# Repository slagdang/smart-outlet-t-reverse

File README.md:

# Smart switched outlet (2025) teardown

## History and product overview

A smart switched outlet is actually a device that plugs into a non-switched
outlet and has its own power outlet on it. The device is controllable remotely
over Wi-Fi and allows the device to be turned on and off.

This smart switched outlet is sold by Tapo.
Tapo describes it as a Matter smart plug.
It uses Matter over IPv6 over WiFi. It does not use Thread.
This is for US voltage and outlets. It was purchased in July 2025.
The device allows switching of the outlet and remote monitoring of
the switch state.

## Electrical background

In the US most appliances use 3-prong plugs with two parallel blade conductors
for the power conduction and a round pin for the protective ground.
The standard outlet for 120V at up to 15A (60Hz) is a NEMA 5-15R.
The plug that goes into it is a NEMA 5-15P.
The power is provided with one blade conductor that is at 120VAC RMS potential
compared to ground (called live, line or hot) and one blade conductor that
is at zero potential compared to ground (called neutral or return).

Protective ground should never be interrupted so that the device is grounded even
when off.
To turn a device off it is only necessary to interrupt the power circuit at any
point. This will cease current flow.
However it is safer to do this by interrupting the live conductor. This means all
circuitry in attached appliance will be at 0V potential as both still connected
conductors are at 0V potential.
To ensure this requires a polarized plug. In the US this is done on
ungrounded plugs with two different sized blades, one too large to fit
in the hot slot. Grounded plugs with the round pin are inherently oriented
and do not need two different-sized blades.

## How it works

This device directly connects ground from the device socket to the wall plug
at all times. It also connects neutral continuously.
It accomplishes its switching by interrupting the live line using a relay.

The relay is controlled using a single bit from a controller board that drives
a GPO line high or low.

## Circuit analysis

[view schematic as a PDF here.](smart-outlet-t-reverse.pdf)

The device contains a transformerless switching power supply to generate a
neutral-referenced 5V supply.
It contains a controller sub-module which has a Realtek Bluetooth radio
and microcontroller (RTL8720CM) which utilizes a supply derived from
the 5.0V supply.
It uses a 277V/16A-rated relay on the live side to turn the connected device
on and off.

The board has about 2mm of creepage to conductors on the live (switched) side.
The protective ground pin is not connected to anything inside except the
output receptacle.
The controller uses a GPO to turn the relay on and off through an NPN transistor.
The power input is fused for the controlling circuitry with a fusible resistor.
The fusible resistor is sleeved in polyolefin heat shrink to protect
against a fuse explosion causing further internal damage like producing
short across the AC.
Power through the unit to the attached device is not protected with a fuse or similar.
The controller board appears to use a 5-pin switching power supply to cut
the provided 5V voltage down to that required by the Realtek MCU.
This is more expensive than an LDO but produces less heat. It saves
up to 700mW continuously versus an LDO.
The power lost in the fusible resistor is probably
several times larger than these savings and thus more than wipes them out.

### Main schematic page

C3 provides power smoothing for the controller board.

### Power supply page

The this uses a sophisticated neutral-referenced transformerless
switch-mode power supply (SMPS). The sophistication is mostly contained
within U1 and will not be fully explained here.

The short version is that U1 takes unregulated energy in and outputs
a reduced regulated voltage. It is capable of converting excess
voltage into increased current similar to how a transformer does
and the power (Watts) in is similar to the power out, just the
available voltage at the output is lower than the input and the
available current is increased inversely. It does this by rapidly
switching its output on and off to send energy into an inductor.
This inductor stores the energy in its magnetic field. It is drawn
off by the devices being supplied. It adjusts its switching duty
cycle so as to send the right amount of energy into the inductor
to match the energy being drawn out of the inductor and thus
keep the inductor voltage relatively constant. The inductor’s
resistance to current change and its ability to store energy in
its magnetic field are critical in making this happen.

Fused AC power at about 120V RMS comes in on FUSED_AC. D1 performs a positive
half-wave rectification on the AC. D2 applies a redundant half-wave
rectification. D2 is present only because diodes have some tendency to
become short circuits when failing. This would put AC voltage into the
circuit and produce a small conflagration within the device. By having two
diodes both D1 and D2 have to fail short to produce this result. This
should reduce the incidence of these small fires to the square of the
incidence rate with a single diode. So if this failure rate would be
one in one thousand over the life of the product then with two
consecutive diodes the failure rate would drop to one in a million
instead.

D2 allows C172 to be filled from FUSED_AC but not emptied. The voltage
on C172 will be relatively constant at the level of the highest positive
voltage on FUSED_AC although it will fall slowly as C172 is drained by
the devices it powers until the next positive AC sine wave arrives to
recharge it. This falling and rising is called ripple.
L1 operates as a filter to prevent high-frequency
voltage changes produced on HVDC from being presented on FUSED_AC. These
changes would produce RF noise on the AC lines which would cause the
device to fail FCC testing. L1 also helps to smooth the ripple from
passing to HVDC. EC2 acts as a final smoothing to make the power as
close to flat DC as possible.

U1 receives its initial power over pin 4. When operating it drives
current through L2 by driving it out through pin 5 into U1_GND
while the internal switch is on. Once it switches off current
continues through the catch diode D3. When operating it receives
its own regulated power output through pin 3 via D11.
C173 serves to smooth this voltage.

The top of C170 will be at the regulated voltage during operation.
R20 serves as a dummy load so as to make regulation easier at low
current draws.

### Power control page

Several functions are provided on this page. The simplest is to connect input
ground directly to the ground on the power outlet side and input neutral
directly to the neutral on the power outlet side.

The second function is to supply AC power to the power supply circuit
so it can create 5V DC power from the AC power. This is done via fuse F1.
F1 is a 10Ω fusible resistor that will fail at high currents due to heat.

The final function is to switch the output live power on and off
using a relay. Relay SW1 connects the output live to the wall source when
energized. SW1 is energized by the controller applying a positive
logic-level voltage on OUTPUT_ON. Once the base (pin 1) of Q2 is 0.6V
or more positive than the emitter (pin 2) then current flows into
the collector (pin 3) and out the emitter. This happens when POWER_EN
is driven high by the controller. This induces a current through R127
and the base. The current will be at least 6mA. This will cause Q1 to
attempt to drive sufficient current through the collector and the coil
of SW1 to energize SW1 fully. D9 serves to snub the voltage the
inductor (coil) in SW1 produces momentarily when Q2 is switched off.
R127 serves to to ensure Q2 turns off when desired.

## Meta-analysis

Any criticisms here are constructive and do not necessarily indicate a serious
flaw in the product.

The power supply chip employed suggests using a full-bridge rectifier for its AC input.
However this design uses half-wave. It does however put two diodes in series so that
a single diode failing short does not produce a short. This is probably a reasonable
design choice.
The switching power supply does not have an English language datasheet so it is
hard to determine if it is used correctly. Nor is it possible to tell the power
rating other than likely being under 1A due to the output capacitor being 10µF. It is
hard to understand how this chip could be designed with a current sense input which
requires a sense resistor so small even for these low current levels that the required
resistance is such that 4 resistors in parallel are needed to produce the value.

The device contains no X-class capacitor at all. This device is relying
on your wall circuit's protection for protection against overcurrent draw by the attached
device.

The device does not have a MOV for inrush limiting and instead seems to rely on
the metal film fusible resistor to control inrush.

The single button on the controlling board is gasketed against the case for some
protection against materials ingress through the button slit.
The ingressing material can still reach the
controlling board but not the high voltage areas. The device of course also has the
receptacle on the front and those are not sealed so water could ingress there also
as it could on any similar device.

The board is laid out in a very straightfoward way using traces for all the controlling
circuity. 3 floods do exist for the current to the controlled device. There are also
strange areas of bumps in the high current floods. I do not know what these are for.

This device uses no components smaller than an 0603.

This device puts the button on the controller board. This means pressing the button is
torquing the controller board in its socket. It is soldered in with a single shear
(attached only at one end) arrangement. Is this a problem? Probably not. It also puts
the LED on the controller board which mostly just means it is smaller and perhaps less
bright.

### teardown images

### Device identification

The device is approximately 60mm wide by 35mm high by 35mm deep (not including prongs).
It has a NEMA 5-15P on the back to plug into a US outlet. It has
a NEMA 5-15R on the front for plugging in the device you wish to switch.
It is rated for 15 amps out and 100-125V (presumably rms) in general use
(resistive load). It is rated for 8A (1kW!) incandescent load and 1/6HP motor load.

On the bottom it is identified as:

Mini Smart WiFi Plug

Model: Tapo 125M

It lists as FCC ID 2AXJ4P125

## Design tools

This is a KiCAD 9.X project. KiCAD is a free electronic design tool [available at kicad.org](https://kicad.org/).

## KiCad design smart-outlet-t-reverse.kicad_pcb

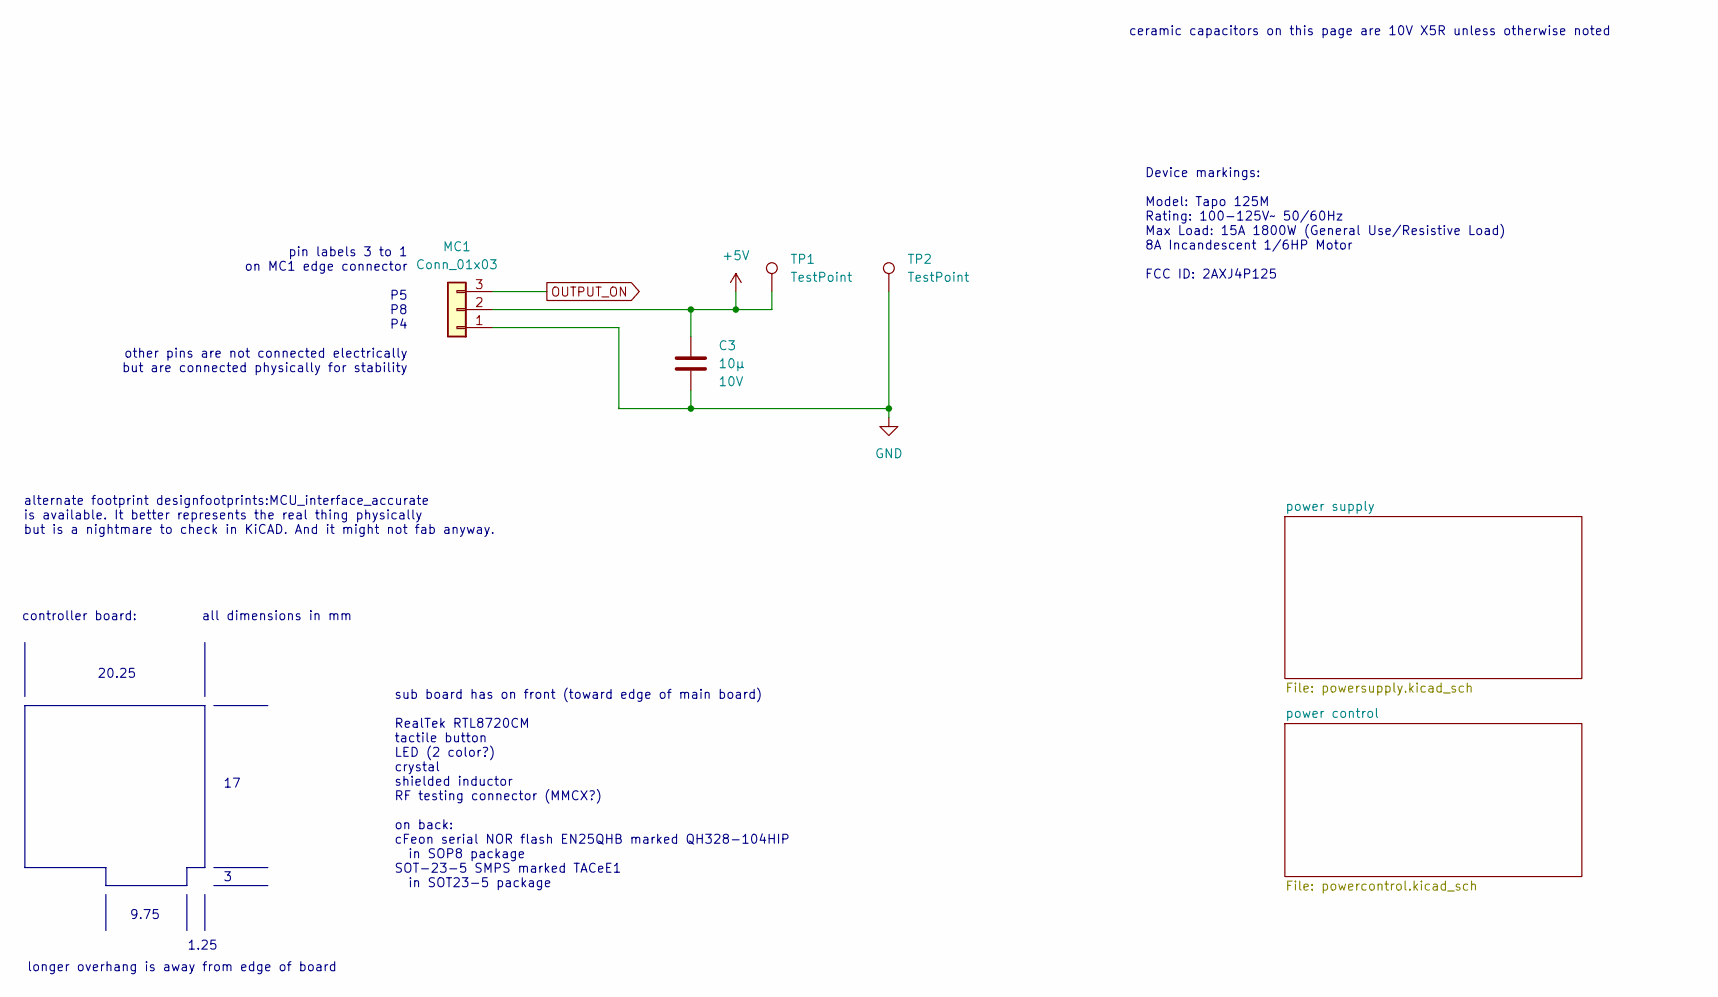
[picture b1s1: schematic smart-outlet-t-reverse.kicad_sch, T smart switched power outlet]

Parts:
C3: 10µ; C_0603_1608Metric; Voltage 10V
MC1: Conn_01x03; MCU_interface
TP1, TP2: TestPoint; TestPoint_Pad_D1.0mm

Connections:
+5V: C3.1, MC1.2, TP1.1; also elsewhere on the board
GND: C3.2, MC1.1, TP2.1; also elsewhere on the board
OUTPUT_ON: MC1.3; also elsewhere on the board

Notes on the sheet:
pin labels 3 to 1 on MC1 edge connector P5 P8 P4 other pins are not connected electrically but are connected physically for stability
Device markings: Model: Tapo 125M Rating: 100-125V~ 50/60Hz Max Load: 15A 1800W (General Use/Resistive Load) 8A Incandescent 1/6HP Motor FCC ID: 2AXJ4P125
alternate footprint designfootprints:MCU_interface_accurate is available. It better represents the real thing physically but is a nightmare to check in KiCAD. And it might not fab anyway.
1.25
9.75
all dimensions in mm
sub board has on front (toward edge of main board) RealTek RTL8720CM tactile button LED (2 color?) crystal shielded inductor RF testing connector (MMCX?) on back: cFeon serial NOR flash EN25QHB marked QH328-104HIP in SOP8 package SOT-23-5 SMPS marked TACeE1 in SOT23-5 package
20.25
ceramic capacitors on this page are 10V X5R unless otherwise noted
longer overhang is away from edge of board
controller board:

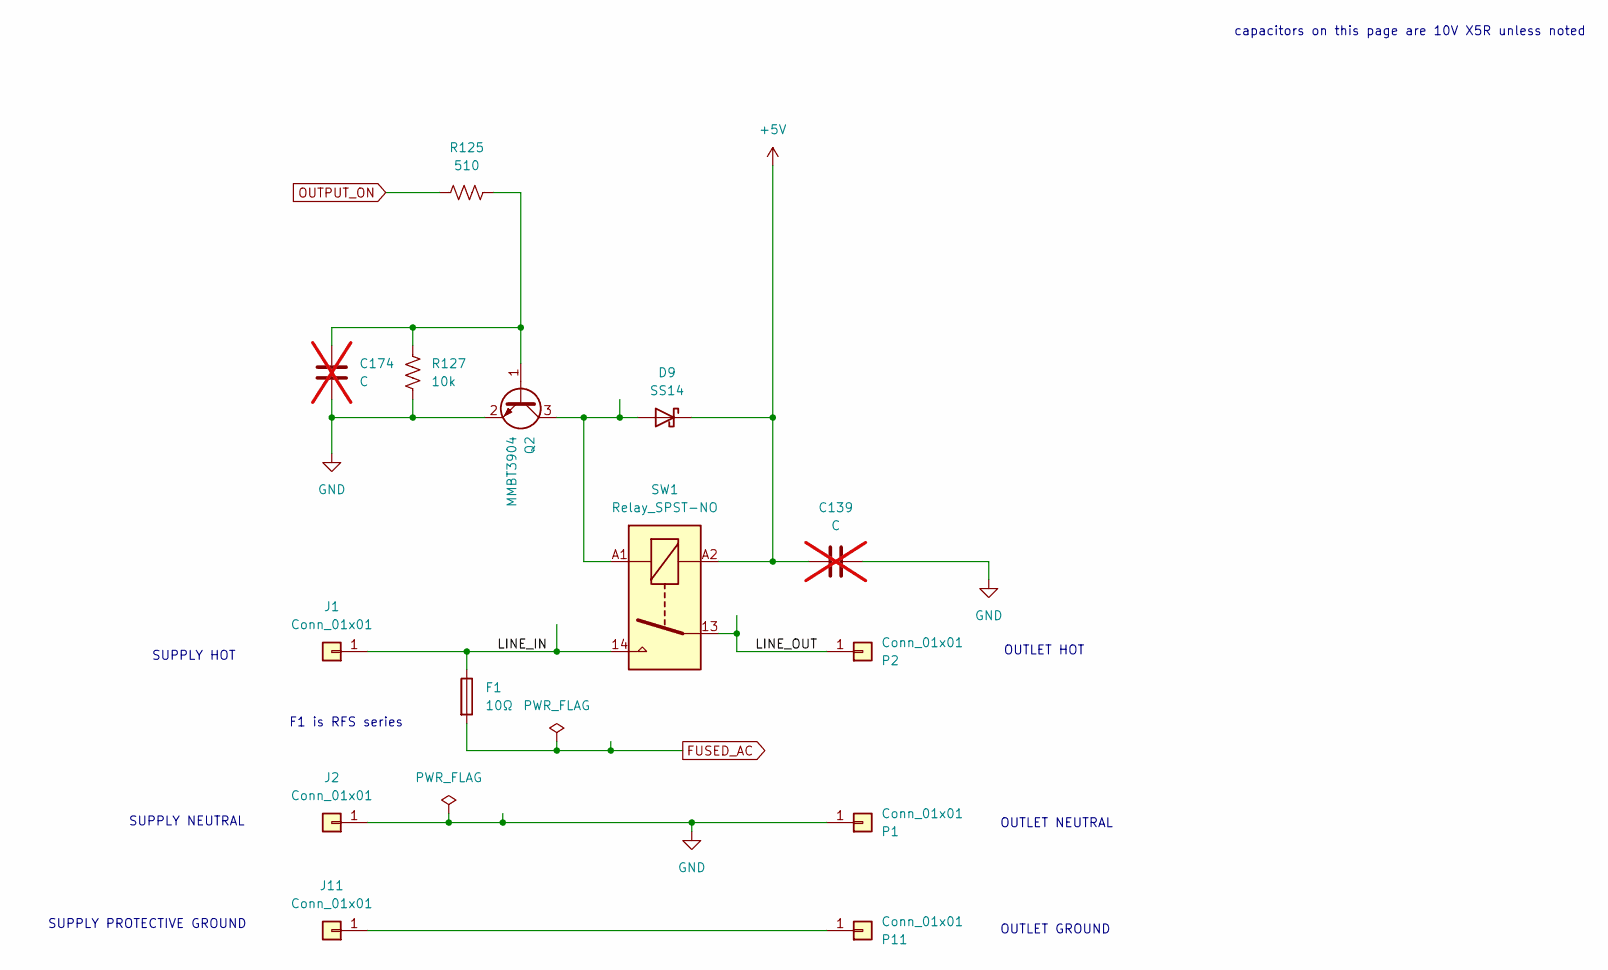
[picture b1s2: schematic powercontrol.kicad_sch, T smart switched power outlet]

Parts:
C139: C; C_0805_2012Metric; not fitted
C174: C; C_0603_1608Metric; not fitted
D9: SS14; D_SOD-123F
F1: 10Ω; R_Axial_DIN0411_L9.9mm_D3.6mm_P5.08mm_Vertical
J1, J2: Conn_01x01; NEMA_5P_pin
J11: Conn_01x01; PinHeader_1x01_P1.00mm_Vertical
P1, P2: Conn_01x01; NEMA_5R_slot
P11: Conn_01x01; PinHeader_1x01_P1.00mm_Vertical
Q2: MMBT3904; SOT-23
R125: 510; R_0603_1608Metric
R127: 10k; R_0603_1608Metric
SW1: Relay_SPST-NO; Relay_SPST_Churod_A16

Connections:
+5V: C139.2, D9.1 (K), SW1.A2; also elsewhere on the board
/power control/LINE_IN: F1.1, J1.1, SW1.14
/power control/LINE_OUT: P2.1, SW1.13
FUSED_AC: F1.2; also elsewhere on the board
GND: C139.1, C174.2, J2.1, P1.1, Q2.2 (E), R127.1; also elsewhere on the board
unnamed: D9.2 (A), Q2.3 (C), SW1.A1
unnamed: J11.1, P11.1
unnamed: C174.1, Q2.1 (B), R125.1, R127.2
OUTPUT_ON: R125.2; also elsewhere on the board

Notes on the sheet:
SUPPLY NEUTRAL
F1 is RFS series
OUTLET GROUND
OUTLET NEUTRAL
SUPPLY HOT
SUPPLY PROTECTIVE GROUND
OUTLET HOT
capacitors on this page are 10V X5R unless noted

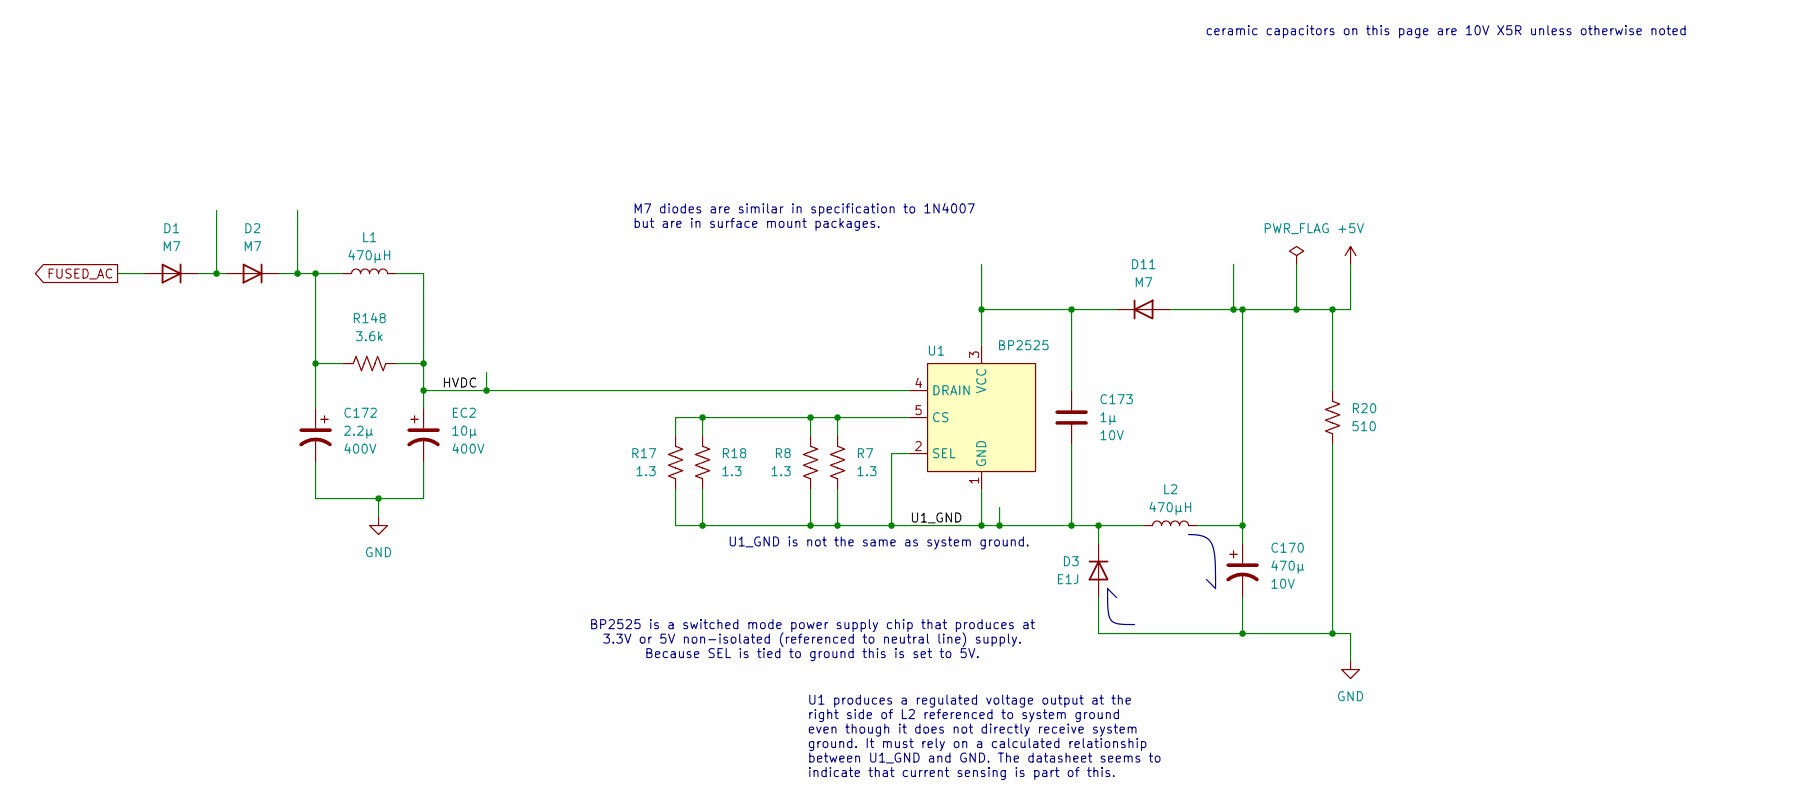
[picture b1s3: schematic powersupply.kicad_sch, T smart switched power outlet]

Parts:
C170: 470µ; CP_Radial_D6.3mm_P2.50mm; Voltage 10V
C172: 2.2µ; CP_Radial_D6.3mm_P2.50mm; Voltage 400V
C173: 1µ; C_0805_2012Metric; Voltage 10V
D1, D2, D11: M7; D_SMA
D3: E1J; D_SOD-123F
EC2: 10µ; CP_Radial_D8.0mm_P3.50mm; Voltage 400V
L1: 470µH; L_Axial_L7.0mm_D3.3mm_P5.08mm_Vertical_Fastron_MICC
L2: 470µH; L_Radial_D8.7mm_P5.00mm_Fastron_07HCP
R7, R8, R17, R18: 1.3; R_0603_1608Metric
R20: 510; R_0603_1608Metric
R148: 3.6k; R_0805_2012Metric
U1: BP2525; BrightSemi_BP2525

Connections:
+5V: C170.1, D11.2 (A), L2.2, R20.2; also elsewhere on the board
/power supply/HVDC: EC2.1, L1.2, R148.2, U1.4 (DRAIN)
/power supply/U1_GND: C173.2, D3.1 (K), L2.1, R7.1, R8.1, R17.1, R18.1, U1.1 (GND), U1.2 (SEL)
FUSED_AC: D1.2 (A); also elsewhere on the board
GND: C170.2, C172.2, D3.2 (A), EC2.2, R20.1; also elsewhere on the board
unnamed: D1.1 (K), D2.2 (A)
unnamed: C172.1, D2.1 (K), L1.1, R148.1
unnamed: C173.1, D11.1 (K), U1.3 (VCC)
unnamed: R7.2, R8.2, R17.2, R18.2, U1.5 (CS)

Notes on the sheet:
ceramic capacitors on this page are 10V X5R unless otherwise noted
M7 diodes are similar in specification to 1N4007 but are in surface mount packages.
U1 produces a regulated voltage output at the right side of L2 referenced to system ground even though it does not directly receive system ground. It must rely on a calculated relationship between U1_GND and GND. The datasheet seems to indicate that current sensing is part of this.
BP2525 is a switched mode power supply chip that produces at 3.3V or 5V non-isolated (referenced to neutral line) supply. Because SEL is tied to ground this is set to 5V.
U1_GND is not the same as system ground.

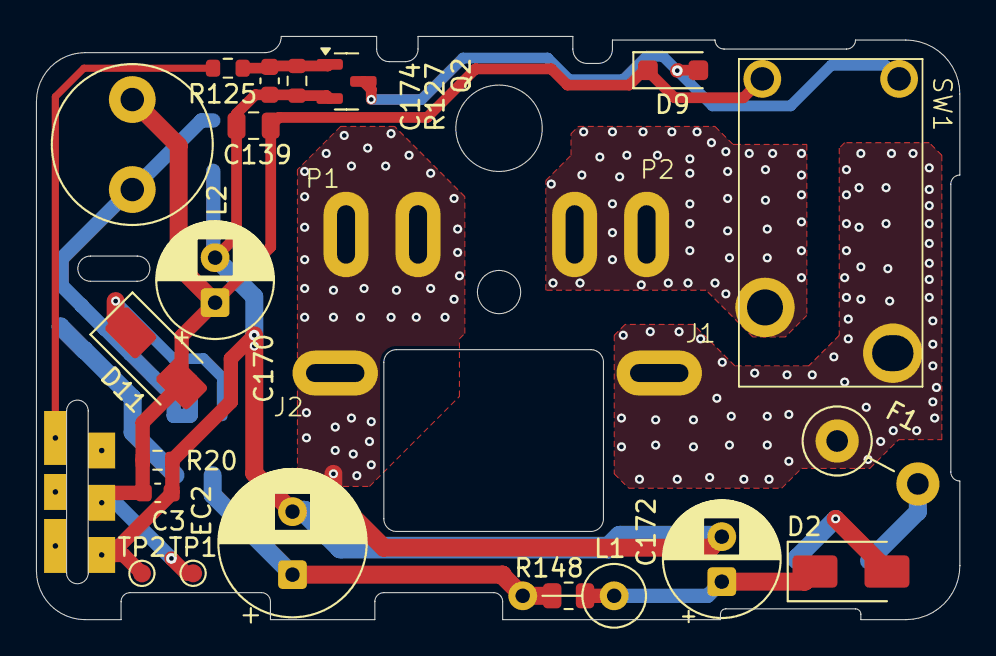
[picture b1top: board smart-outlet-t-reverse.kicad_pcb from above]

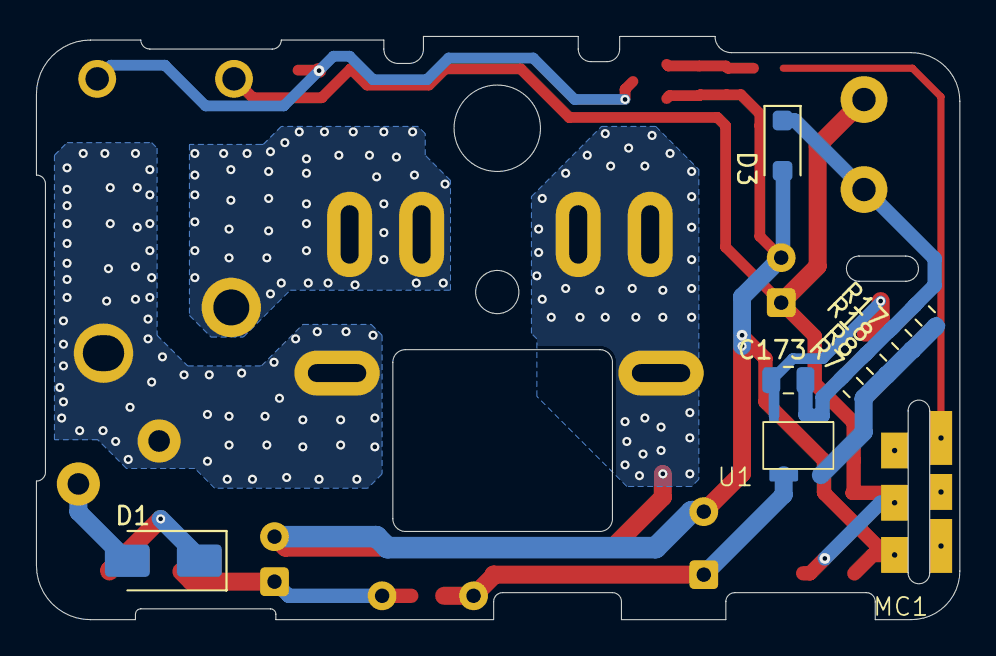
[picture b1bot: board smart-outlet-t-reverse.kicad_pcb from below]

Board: 2 copper layers, 51.3 x 32.4 mm, 33 parts (9 on the bottom side), 14 nets.

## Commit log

2025-08-01 Just getting started. Still has background picture to trace. Do not push that to master.
2025-08-01 Looking quite accurate. Time to fix connector foots.
2025-08-02 Added vias. Proper connector holes for socket and plug. Now final cleanups mostly.
2025-08-02 Fixed MC1 footprint. Now it produces errors aplenty.
2025-08-02 Settled on MC1 layout. A bit more routing cleanup. Really down to fab and silk now. Plus some work on F1.
2025-08-02 Cleaned schematic. Still have silk and fab to do. Also have not fixed F1. Have decided I may not fix F1.
2025-08-02 Added description of microcontroller subboard to schematic.
2025-08-02 Fab set. Silk set. I think it is done.
2025-08-02 Removed background picture.
2025-08-02 bring LICENSE and readme from github
2025-08-17 Updating project to describe itself better.
2025-08-18 Updated README to be more detailed. Updated schematic to pass checks and regenerated PDF. Added a few comments. Updated pcb from schematic changes.
2025-11-30 Rerender PF as github.io refuses to render the previous one. I have no way to check to see if github.io will render this one without uploading it.
2025-11-30 Previous PDF rendered fine on github. However, it was missing the schematic sheet markings. Rerendered again. Hopefully this is the last.
